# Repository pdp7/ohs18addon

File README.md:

# ohs18addon
OSHWA-themed Learn to Solder add-on board for the Open Hardware Summit 2018 badge

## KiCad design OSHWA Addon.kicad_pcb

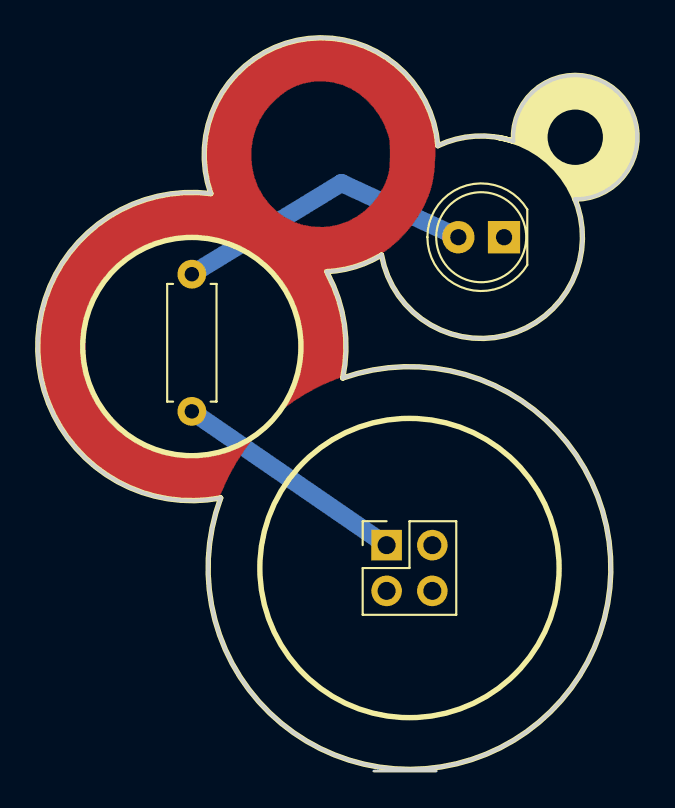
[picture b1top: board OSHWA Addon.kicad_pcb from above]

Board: 2 copper layers, 33.3 x 40.6 mm, 3 parts (0 on the bottom side), 3 nets.

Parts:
D1: LED; LED_D5.0mm_Clear
J1: Conn_02x02_Counter_Clockwise; PinHeader_2x02_P2.54mm_Vertical
R1: R; R_Axial_DIN0207_L6.3mm_D2.5mm_P7.62mm_Horizontal

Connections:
unnamed: D1.1, J1.3
unnamed: D1.2, R1.2
unnamed: J1.1, R1.1

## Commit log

2018-09-01 initial check in of files from Andrew Sowa
2018-09-07 update silkscreen text
2018-09-07 update silkscreen, add line to bottom circle to avoid gerbv bug
2018-09-07 update silkscreen
